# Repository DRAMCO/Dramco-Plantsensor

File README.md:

# Dramco Plantsensor

## How it works
The Dramco Plantsensor measures the moisture level of the soil every 30 seconds. When the soil is dry, the green LED will start blinking (first rapidly to get your attention, after a while it will slow down to every 30 seconds). The battery is running low when the red LED also starts blinking. If you have the rechargeable version, you can recharge using the micro USB connection on top. If not, replace the battery (you can also power the sensor of a USB cable). 

## How to assemble
When you get your Dramco Plantsensor, some components still need to be soldered. Solder all through hole components to complete the sensor. More information in this pdf. Don't forget to add a battery. 

## How to program
To program the Dramco Plantsensor, you'll need a [Dramco Uno as ATTINY85 programmer](https://create.arduino.cc/projecthub/arjun/programming-attiny85-with-arduino-uno-afb829), some [POGO pins](https://benl.rs-online.com/web/p/test-pins/1613648/?cm_mmc=BE-PLA-DS3A-_-google-_-CSS_BE_NL_Test_%26_Measurement_Whoop-_-(BE:Whoop!)+Test+Probes-_-1613648&matchtype=&pla-339422850668&gclid=Cj0KCQjwwNWKBhDAARIsAJ8HkhclvIvYQJyAc5_Ah08zPnTl_AxyPAWuMrbqTGvm6uMTI3wQCO1g0-QaAm2mEALw_wcB&gclsrc=aw.ds) and the [Arduino IDE](https://www.arduino.cc/en/software) installed. The pinout of the programming pads, is shown in the schematics. Adapt and use the following command to program: 
 ```
 "C:\Program Files (x86)\Arduino\hardware\tools\avr/bin/avrdude" -C"C:\Program Files (x86)\Arduino\hardware\tools\avr/etc/avrdude.conf" -v -pattiny85 -cstk500v1 -PCOM4 -b19200 -Uflash:w:"Soil_sensor.hex":i -U lfuse:w:0xF1:m -U hfuse:w:0x57:m -U efuse:w:0xFE:m
 ```
(!) This command disables the RESET pin of the ATTINY85, use only if you have a [high voltage flash programmer](https://td0g.ca/2020/04/13/high-voltage-flash-programming-on-attiny85/).

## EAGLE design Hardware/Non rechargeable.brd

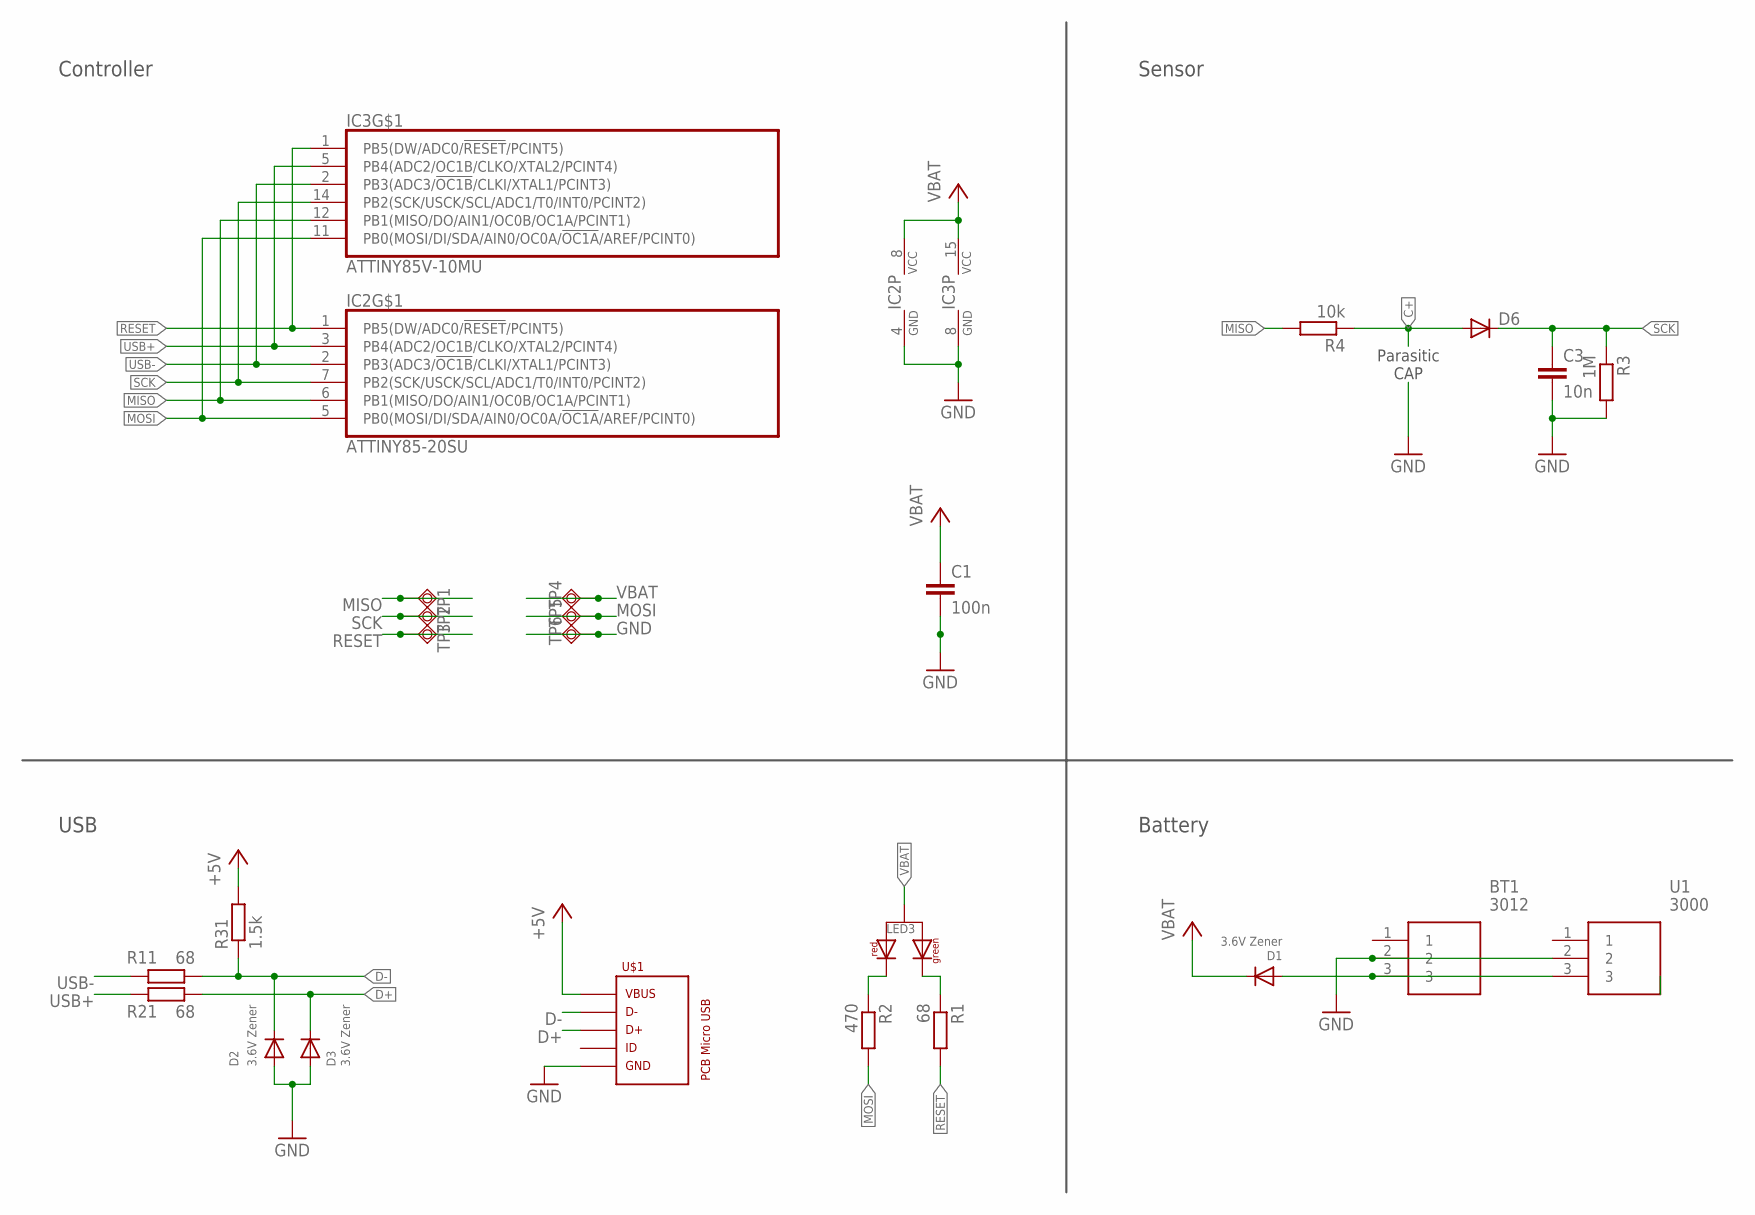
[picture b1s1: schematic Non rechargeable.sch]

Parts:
BT1: 3012
C1: 100n; C0603
C3: 10n; C025-024X044
D1, D2, D3: 3.6V Zener; SOD-323F
D6: DIODE-D-5; D-5
IC2: ATTINY85-20SU; 8S2
IC3: ATTINY85V-10MU; QFN20_4X4_0.50
LED3: KPBA-3010SURKCGKC3MM; 3MMLED
R1: 68; 0204/7
R2: 470; 0204/7
R3: 1M; 0204/7
R4: 10k; 0204/7
R11, R21: 68; R0603
R31: 1.5k; R0603
TP1, TP2, TP3, TP4, TP5: TPSQTP15R; TP15R
TP6: TPSQTP15SQ; TP15SQ
U1: 3000
U$1: PCB_MICRO_USB_BSS_3; USB_TYPE_B_SS_3

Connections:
C+: D6.A, R4.1
D+: D3.C, R21.1, U$1.3
D-: D2.C, R11.1, R31.1, U$1.2
GND: BT1.2, C1.2, C3.2, D2.A, D3.A, IC2.4 (GND), IC3.8 (GND), R3.2, TP6.TP, U1.2, U$1.5
MISO: IC2.6 (PB1(MISO/DO/AIN1/OC0B/OC1A/PCINT1)), IC3.12 (PB1(MISO/DO/AIN1/OC0B/OC1A/PCINT1)), R4.2, TP1.TP
MOSI: IC2.5 (PB0(MOSI/DI/SDA/AIN0/OC0A/!OC1A!/AREF/P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), IC3.11 (PB0(MOSI/DI/SDA/AIN0/OC0A/!OC1A!/AREF/P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), R2.2, TP5.TP
unnamed: LED3.-2, R1.1
unnamed: LED3.-1, R2.1
RESET: IC2.1 (PB5(DW/ADC0/!RESET!/PCINT5)), IC3.1 (PB5(DW/ADC0/!RESET!/PCINT5)), R1.2, TP3.TP
SCK: C3.1, D6.C, IC2.7 (PB2(SCK/USCK/SCL/ADC1/T0/INT0/PCINT2)), IC3.14 (PB2(SCK/USCK/SCL/ADC1/T0/INT0/PCINT2)), R3.1, TP2.TP
USB+: IC2.3 (PB4(ADC2/OC1B/CLKO/XTAL2/PCINT4)), IC3.5 (PB4(ADC2/OC1B/CLKO/XTAL2/PCINT4)), R21.2
USB-: IC2.2 (PB3(ADC3/!OC1B!/CLKI/XTAL1/PCINT3)), IC3.2 (PB3(ADC3/!OC1B!/CLKI/XTAL1/PCINT3)), R11.2
VB: BT1.3, D1.A, U1.3
VBAT: C1.1, D1.C, IC2.8 (VCC), IC3.15 (VCC), LED3.+, R31.2, TP4.TP, U$1.1

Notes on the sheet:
Controller
USB
Battery
Parasitic CAP
Sensor

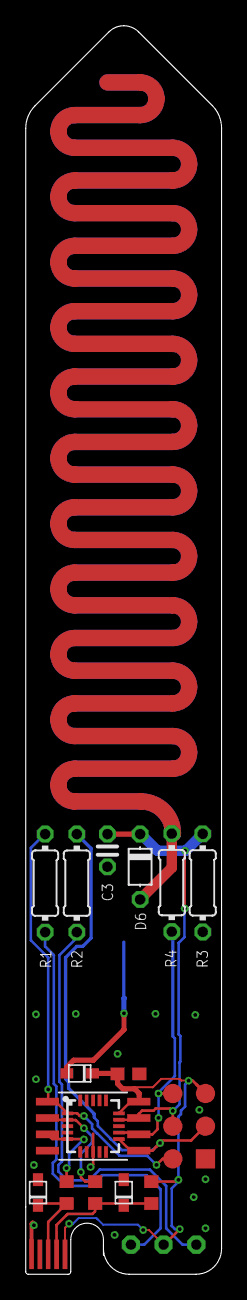
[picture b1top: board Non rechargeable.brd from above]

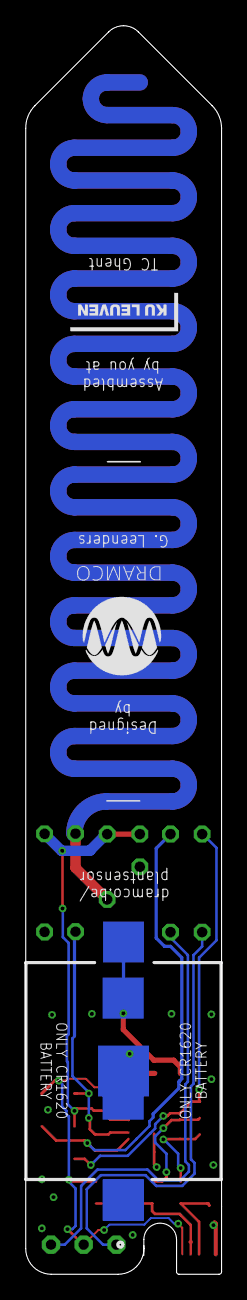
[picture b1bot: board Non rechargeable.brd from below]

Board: 2 copper layers, 15.2 x 97.0 mm, 25 parts (2 on the bottom side), 14 nets.

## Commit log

2021-09-30 Added some pictures
2021-09-30 Trying out video
2021-09-30 Added gif
